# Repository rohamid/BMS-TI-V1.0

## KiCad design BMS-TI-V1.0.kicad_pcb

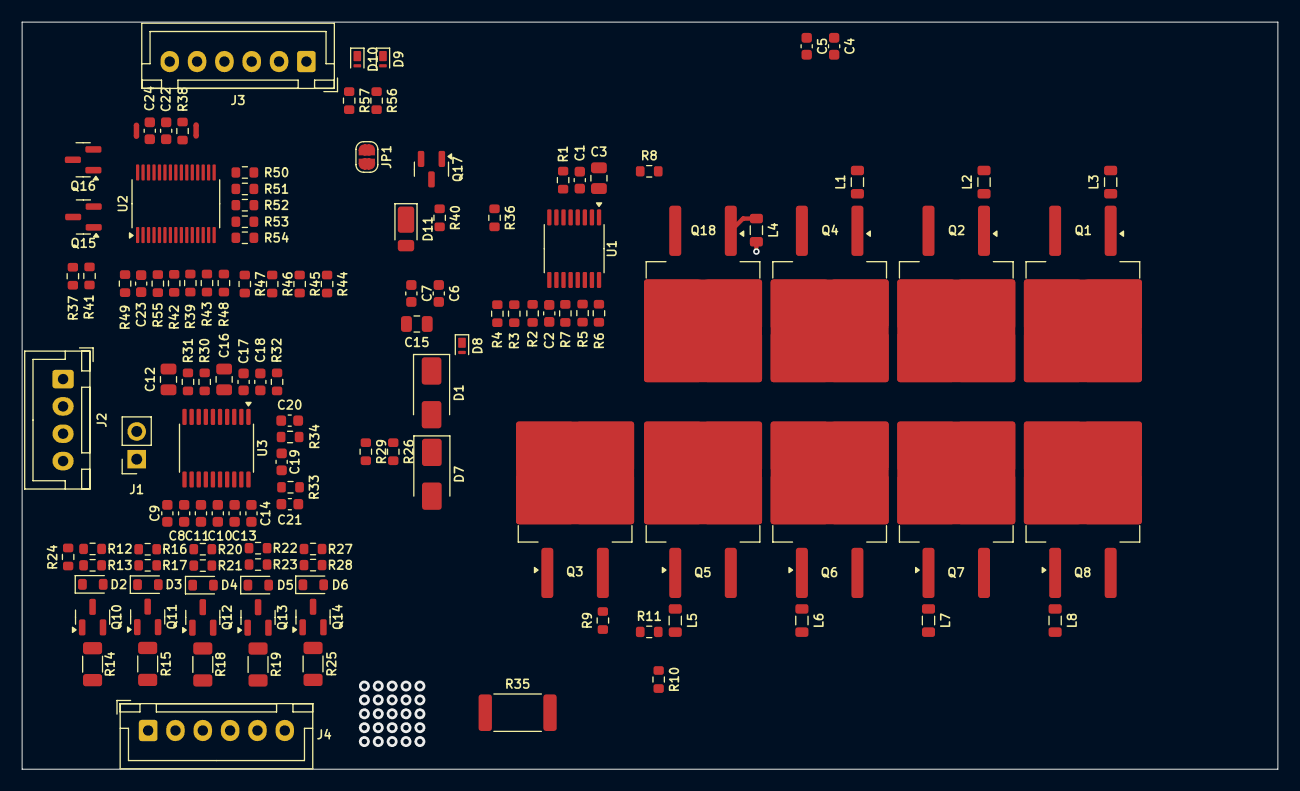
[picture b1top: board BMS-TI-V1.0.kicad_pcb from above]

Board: 2 copper layers, 114.9 x 68.4 mm, 127 parts (0 on the bottom side), 90 nets.

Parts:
C1, C2: 10n; C_0603_1608Metric
C3, C12: 2u2; C_0805_2012Metric
C4, C5, C6, C7, C19, C20, C21, C22, C24: 100n; C_0603_1608Metric
C8, C9, C10, C11, C13, C14: 220n; C_0603_1608Metric
C15: 4u7; C_0805_2012Metric
C16: 1u; C_0805_2012Metric
C17: 4700p; C_0603_1608Metric
C18: 470p; C_0603_1608Metric
C23: 3300p; C_0603_1608Metric
D1, D7: D; D_SMA
D2, D3, D4, D5, D6: 5.6V; D_SOD-110
D8, D9, D10: PTVS5V0Z1USK; Nexperia_DSN1608-2_1.6x0.8mm
D11: 15V; D_PowerDI-123
J1: Thermistor; PinSocket_1x02_P2.54mm_Vertical
J2: Conn_01x04; JST_XH_B4B-XH-A_1x04_P2.50mm_Vertical
J3: LED; JST_XH_B6B-XH-A_1x06_P2.50mm_Vertical
J4: Conn_01x06; JST_XH_B6B-XH-A_1x06_P2.50mm_Vertical
JP1: PRECH_EN; SolderJumper-2_P1.3mm_Open_RoundedPad1.0x1.5mm
L1, L2, L3, L4, L5, L6, L7, L8: 600R; L_0805_2012Metric
NT1, NT2: NetTie_2; NetTie-2_SMD_Pad0.5mm
Q1, Q2, Q3, Q4, Q5, Q6, Q7, Q8, Q18: IRFS4115; TO-263-2
Q10, Q11, Q12, Q13, Q14, Q16, Q17: 2N7002; SOT-23
Q15: BSS84; SOT-23
R1, R2: 100R; R_0603_1608Metric
R3, R37: 300K; R_0603_1608Metric
R4: 11.3K; R_0603_1608Metric
R5, R6, R7: 0; R_0603_1608Metric
R8, R10, R11: 10M; R_0603_1608Metric
R9, R13, R17, R21, R23, R24, R28: 1K; R_0603_1608Metric
R12, R16, R20, R22, R26, R27, R30, R31: 10K; R_0603_1608Metric
R14, R15, R18, R19, R25: 28.7; R_1206_3216Metric
R29, R33, R34, R42, R43, R46, R47: 100; R_0603_1608Metric
R32: 499K; R_0603_1608Metric
R35: 0.0015; R_2512_6332Metric
R36, R38, R40, R49, R55: 100K; R_0603_1608Metric
R39, R44, R45: 1M; R_0603_1608Metric
R41: 13.7K; R_0603_1608Metric
R48: 221K; R_0603_1608Metric
R50, R51, R52, R53, R54: 330K; R_0603_1608Metric
R56: 49.9K; R_0603_1608Metric
R57: 195K; R_0603_1608Metric
U1: BQ76200PW; TSSOP-16_4.4x5mm_P0.65mm
U2: BQ78350DBT; TSSOP-30_4.4x7.8mm_P0.5mm
U3: BQ76920PW; TSSOP-20_4.4x6.5mm_P0.65mm

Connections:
+BATT: C4.1, D8.1 (K), D11.1 (K), Q1.3 (S), Q2.3 (S), Q4.3 (S), Q15.2 (S), Q18.3 (S), R1.1, R8.1, R9.1, R36.1
+PACK: C5.2, C6.2, D1.1 (K), Q5.3 (S), Q6.3 (S), Q7.3 (S), Q8.3 (S), R2.1, R11.1
-BATT: D8.2 (A), D9.2 (A), D10.2 (A), R33.1, R35.1
-PACK: C7.1, D1.2 (A), R34.1, R35.2
/BAT-AFE/ALERT: C18.1, R32.2, U2.2 (ALERT), U3.20 (ALERT)
/BAT-AFE/BAT-: D6.2 (A), J4.6, Q14.2 (S), R28.1
/BAT-AFE/BOOT: C17.1, J1.1, U3.6 (TS1)
/BAT-AFE/C1: D5.2 (A), J4.5, Q13.2 (S), R23.1, R25.1
/BAT-AFE/C2: D4.2 (A), J4.4, Q12.2 (S), R19.1, R21.1
/BAT-AFE/C3: D3.2 (A), J4.3, Q11.2 (S), R17.1, R18.1
/BAT-AFE/C4: D2.2 (A), J4.2, Q10.2 (S), R13.1, R15.1
/BAT-AFE/C5: D7.2 (A), J4.1, R14.1, R24.1, R26.1
/BAT-AFE/CAP1: C16.1, U3.7 (CAP1)
/BAT-AFE/CHG: U1.4 (CHG_EN), U3.2 (CHG)
/BAT-AFE/DSG: U1.6 (DSG_EN), U3.1 (DSG)
/BAT-AFE/SCL: R31.1, U2.4 (SCL), U3.5 (SCL)
/BAT-AFE/SDA: R30.1, U2.3 (SDA), U3.4 (SDA)
/BAT-SWITCH/DIVP: R3.2, R4.1
/BAT-SWITCH/DRAIN: Q1.2 (D), Q2.2 (D), Q3.2 (D), Q4.2 (D), Q5.2 (D), Q6.2 (D), Q7.2 (D), Q8.2 (D), Q18.2 (D), R10.2
/BAT-SWITCH/PCHG_EN: R49.2, U1.8 (PCHG_EN), U2.5 (~PRECHG)
/GAS-GAUGE-COMPANION/~KEYIN: R55.2, U2.9 (~KEYIN)
GND: C1.2, C2.2, C12.2, C14.2, C15.2, C16.2, C17.2, C18.2, C20.2, C21.1, C22.2, C23.1, C24.2, J1.2, J2.4, NT1.1, NT2.1, Q16.2 (S), Q17.2 (S), R4.2, R32.1, R41.1, R44.2, R45.2, U1.9 (VSS), U2.6 (VAUX), U2.22 (VSS), U2.23 (VSS), U2.25 (VSS), U3.3 (VSS)
unnamed: C4.2, C5.1
unnamed: C6.1, C7.2
unnamed: D2.1 (K), Q10.1 (G), R12.1
unnamed: D3.1 (K), Q11.1 (G), R16.1
unnamed: D4.1 (K), Q12.1 (G), R20.1
unnamed: D5.1 (K), Q13.1 (G), R22.1
unnamed: D6.1 (K), Q14.1 (G), R27.1
unnamed: D7.1 (K), R26.2, R29.2
unnamed: D9.1 (K), R43.2, R44.1, R46.1
unnamed: D10.1 (K), R42.2, R45.1, R47.1
unnamed: D11.2 (A), Q15.1 (G), R36.2, R40.1
unnamed: J2.2, R47.2
unnamed: J2.3, R46.2
unnamed: J3.1, R50.2, U2.16 (LED1)
unnamed: J3.2, R51.2, U2.17 (LED2)
unnamed: J3.3, R52.2, U2.18 (LED3)
unnamed: J3.4, R53.2, U2.19 (LED4)
unnamed: J3.5, R54.2, U2.20 (LED5)
unnamed: J3.6, U2.1 (COM)
unnamed: JP1.1 (A), R49.1
unnamed: L1.2, L2.2, L3.2, L4.2, R6.2, R8.2
unnamed: L5.2, L6.2, L7.2, L8.2, R7.2, R11.2
unnamed: L3.1, Q1.1 (G)
unnamed: L2.1, Q2.1 (G)
unnamed: Q3.1 (G), R5.2, R10.1
unnamed: Q3.3 (S), R9.2
unnamed: L1.1, Q4.1 (G)
unnamed: L5.1, Q5.1 (G)
unnamed: L6.1, Q6.1 (G)
unnamed: L7.1, Q7.1 (G)
unnamed: L8.1, Q8.1 (G)
unnamed: Q10.3 (D), R14.2
unnamed: Q11.3 (D), R15.2
unnamed: Q12.3 (D), R18.2
unnamed: Q13.3 (D), R19.2
unnamed: Q14.3 (D), R25.2
unnamed: Q15.3 (D), R37.1
unnamed: Q16.3 (D), R56.2
unnamed: Q16.1 (G), U2.29 (ADREN)
unnamed: Q17.3 (D), R40.2
unnamed: Q17.1 (G), R39.1, U2.12 (VEN)
unnamed: L4.1, Q18.1 (G)
unnamed: C1.1, C3.2, R1.2, U1.2 (BAT)
unnamed: R6.1, U1.16 (CHG)
unnamed: R7.1, U1.12 (DSG)
unnamed: C2.1, R2.2, U1.11 (PACK)
unnamed: R3.1, U1.10 (PACKDIV)
unnamed: R5.1, U1.14 (PCHG)
unnamed: C3.1, U1.1 (VDDCP)
unnamed: C23.2, R37.2, R41.2, U2.7 (BAT)
unnamed: NT1.2, U2.21 (GPIO_A)
unnamed: NT2.2, U2.28 (GPIO_B)
unnamed: C24.1, U2.27 (RBI)
unnamed: R56.1, R57.2, U2.30 (SMBA)
unnamed: R43.1, U2.13 (SMBC)
unnamed: R42.1, U2.11 (SMBD)
unnamed: R48.2, U2.14 (~DISP)
unnamed: R38.2, U2.24 (~MRST)
unnamed: C12.1, R29.1, U3.9 (REGSRC), U3.10 (BAT)
unnamed: C19.2, C20.1, R34.2, U3.19 (SRN)
unnamed: C19.1, C21.2, R33.2, U3.18 (SRP)
unnamed: C13.2, C14.1, R27.2, R28.2, U3.17 (VC0)
unnamed: C10.2, C13.1, R22.2, R23.2, U3.16 (VC1)
unnamed: C10.1, C11.2, R20.2, R21.2, U3.15 (VC2)
unnamed: C8.2, C11.1, R16.2, R17.2, U3.14 (VC3)
unnamed: C8.1, C9.2, R12.2, R13.2, U3.13 (VC4)
unnamed: C9.1, R24.2, U3.12 (VC5)
VREGOUT: C15.1, C22.1, JP1.2 (B), R30.2, R31.2, R38.1, R39.2, R48.1, R50.1, R51.1, R52.1, R53.1, R54.1, R55.1, R57.1, U2.26 (VCC), U3.8 (REGOUT)

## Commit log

2025-01-07 Added BQ78350 Gas-gauge companion
2025-01-08 Changes Mosfet's package to D2PAK
